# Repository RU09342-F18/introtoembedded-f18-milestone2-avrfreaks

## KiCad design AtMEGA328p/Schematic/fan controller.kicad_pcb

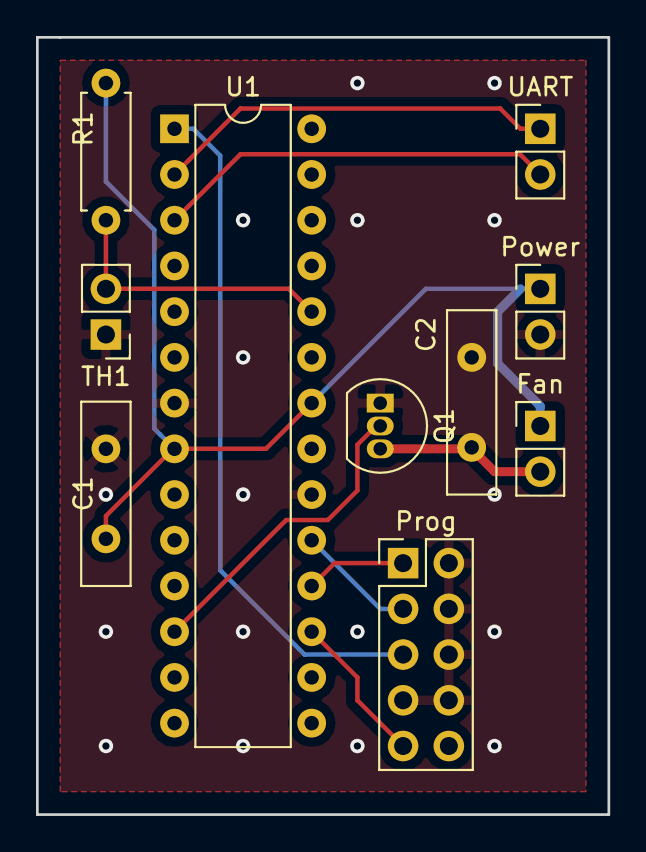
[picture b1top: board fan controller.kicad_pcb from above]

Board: 2 copper layers, 31.8 x 43.2 mm, 10 parts (0 on the bottom side), 11 nets.

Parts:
C1, C2: 0.1u; C_Disc_D10.0mm_W2.5mm_P5.00mm
Fan: Fan; PinHeader_1x02_P2.54mm_Vertical
Power: PinHeader_1x02_P2.54mm_Vertical
Prog: Conn_02x05_Counter_Clockwise; PinHeader_2x05_P2.54mm_Vertical
Q1: 2N7000; TO-92_Inline
R1: 6800; R_Axial_DIN0207_L6.3mm_D2.5mm_P7.62mm_Horizontal
TH1: Thermistor; PinHeader_1x02_P2.54mm_Vertical
U1: ATmega328P-PU; DIP-28_W7.62mm
UART: PinHeader_1x02_P2.54mm_Vertical

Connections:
unnamed: C1.1, C2.1, Power.2, Prog.2, Prog.4, Prog.6, Prog.7, Prog.8, Q1.1, TH1.1, U1.7, U1.20
unnamed: C1.2, Fan.1, Power.1, R1.2, U1.8, U1.22
unnamed: Prog.9, U1.17
unnamed: Prog.5, U1.1
unnamed: Prog.3, U1.19
unnamed: Prog.1, U1.18
unnamed: C2.2, Fan.2, Q1.3
unnamed: Q1.2, U1.12
unnamed: R1.1, TH1.2, U1.24
unnamed: U1.2, UART.1
unnamed: U1.3, UART.2

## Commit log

2018-11-30 tuned PID and added sleep modes
2018-11-30 added uart reference setting ability
2018-12-01 Added Appnote
2018-12-01 updated schematic
2018-12-01 added comments
2018-12-02 Added thermistor part number
